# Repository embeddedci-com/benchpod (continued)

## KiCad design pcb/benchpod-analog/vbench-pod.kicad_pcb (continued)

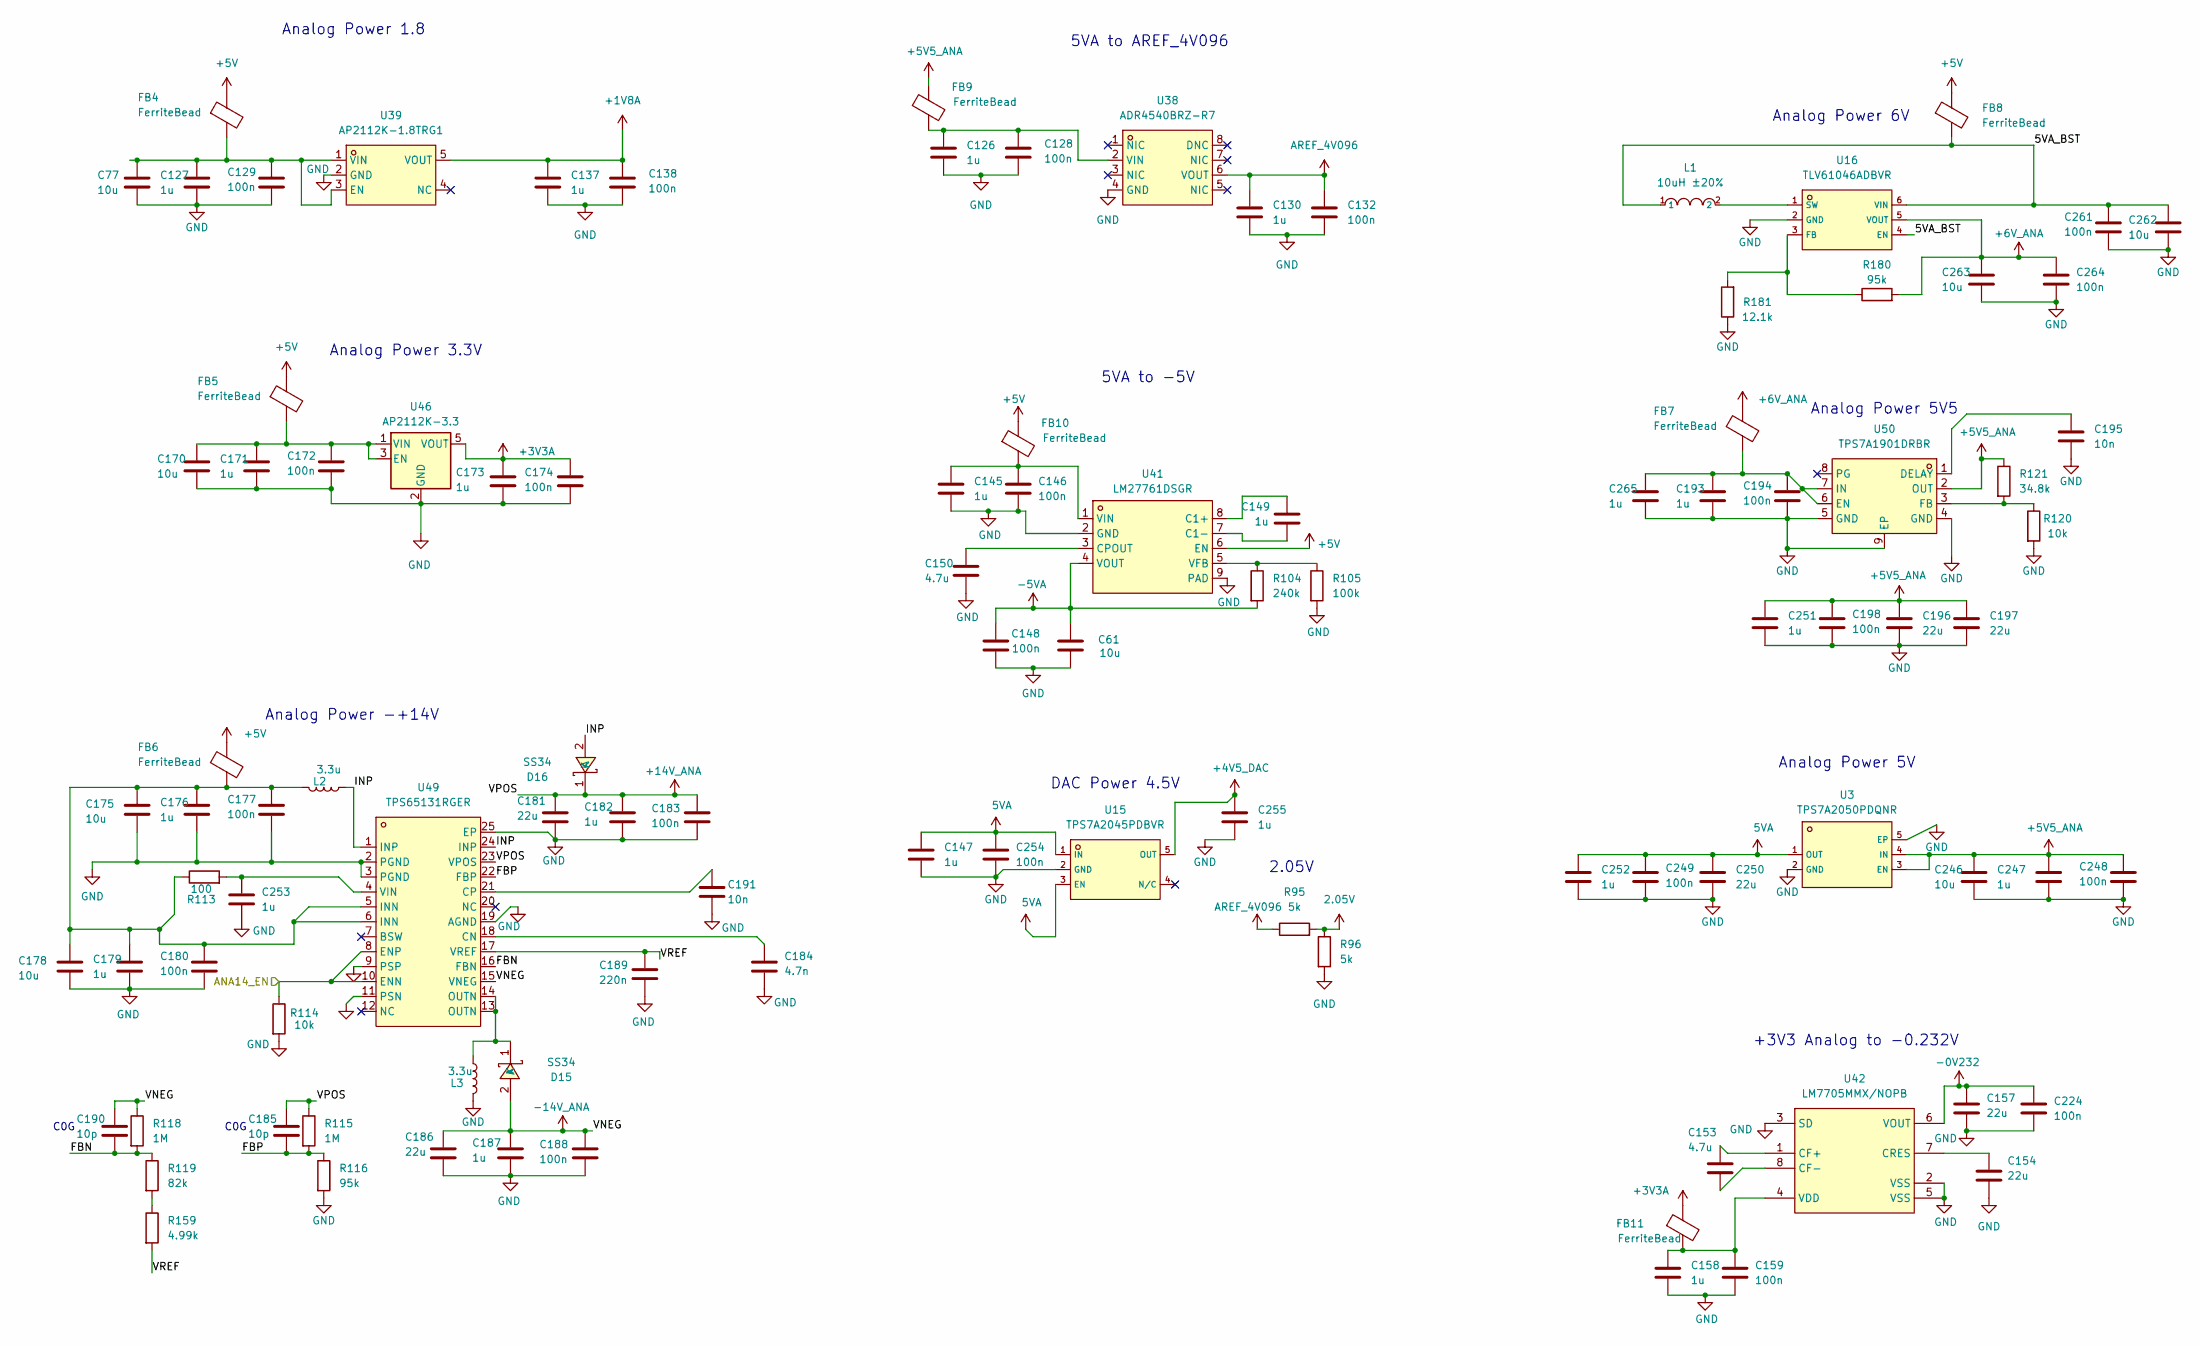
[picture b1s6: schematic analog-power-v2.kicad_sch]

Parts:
C61: 10u; C_0603_1608Metric; LCSC C96446
C77, C170, C175, C178, C246, C262, C263: 10u; C_0603_1608Metric; MPN GRM21BR61H106KE43L; LCSC C96446
C126, C130, C137, C145, C149, C158, C173, C176, C179, C182, C187, C193, C253, C255, C265: 1u; C_0402_1005Metric; MPN GRM155R61H105KE05D; LCSC C1518208
C127, C147, C171, C247, C251, C252: 1u; C_0402_1005Metric; MPN CL05A105KA5NQNC; LCSC C52923
C128, C129, C132, C138, C146, C148, C159, C172, C174, C177, C180, C183, C188, C194, C198, C224, C248, C249, C254, C261, C264: 100n; C_0402_1005Metric; MPN CC0603KRX7R9BB104; LCSC C307331
C150, C153: 4.7u; C_0805_2012Metric; LCSC C98192
C154, C157, C196, C197, C250: 22u; C_0805_2012Metric; LCSC C45783
C181, C186: 22u; C_0805_2012Metric; MPN CL21B105KBFNNNE; LCSC C45783
C184: 4.7n; C_0402_1005Metric; MPN CC0603KRX7R9BB104; LCSC C1538
C185, C190: 10p; C_0402_1005Metric; LCSC C32949
C189: 220n; C_0603_1608Metric; LCSC C64705
C191, C195: 10n; C_0402_1005Metric; LCSC C15195
D15, D16: SS34; SMA_L4.3-W2.6-LS5.2-RD; MPN SS34; LCSC Part C3014011
FB4, FB5, FB6, FB7, FB8, FB9, FB10, FB11: FerriteBead; C85833_L0603; LCSC C85833
L1: 10uH ±20%; C38117_IND-SMD_L4_0-W4_0; LCSC C38117
L2, L3: 3.3u; IND-SMD_L2.0-W1.6_AOTA-B201610S3R3-101-T; LCSC C42411119
R95, R96: 5k; R_0402_1005Metric; LCSC C5948099
R104: 240k; R_0402_1005Metric; LCSC C64043
R105: 100k; R_0402_1005Metric; LCSC C25741
R113: 100; R_0402_1005Metric; LCSC C25076
R114, R120: 10k; R_0402_1005Metric; LCSC C25744
R115, R118: 1M; R_0603_1608Metric; LCSC C22935
R116, R180: 95k; R_0402_1005Metric; LCSC C22375098
R119: 82k; R_0603_1608Metric; LCSC C23254
R121: 34.8k; R_0402_1005Metric; LCSC C2998092
R159: 4.99k; R_0603_1608Metric; LCSC C23046
R181: 12.1k; R_0402_1005Metric; LCSC C25852
U3: TPS7A2050PDQNR; C2866499_X2SON-4_L1_0-W1_0-P0_65-TL-EP; LCSC C2866499
U15: TPS7A2045PDBVR; C2873627_SOT-23-5_L2_9-W1_6-P0_95-LS2_8-BR; LCSC C2873627
U16: TLV61046ADBVR; C464815_SOT-23-6_L2_9-W1_6-P0_95-LS2_8-BL; LCSC C464815
U38: ADR4540BRZ-R7; SOIC-8_L4.9-W3.9-P1.27-LS6.0-BL; MPN ADR4540BRZ-R7; LCSC Part C404003
U39: AP2112K-1.8TRG1; SOT-25_L3.0-W1.6-P0.95-LS2.8-BL; MPN AP2112K-1.8TRG1; LCSC Part C176944
U41: LM27761DSGR; WSON-8_L2.0-W2.0-P0.65-BL-EP; MPN LM27761DSGR; LCSC Part C129351
U42: LM7705MMX/NOPB; MSOP-8_L3.0-W3.0-P0.65-LS5.0-BL; MPN LM7705MMX/NOPB; LCSC Part C2070761
U46: AP2112K-3.3; SOT-25-5_L2.9-W1.6-P0.95-LS2.8-BL; LCSC C51118
U49: TPS65131RGER; VQFN-24_L4.0-W4.0-P0.50-BL-EP2.5; LCSC Part C87663
U50: TPS7A1901DRBR; TDFN-8_L3.0-W3.0-P0.65-BL-EP; MPN TPS7A1901DRBR; LCSC Part C544334

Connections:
2.05V: R95.2, R96.1; also elsewhere on the board
5VA: C147.2, C249.2, C250.1, C252.2, C254.2, U3.1 (OUT), U15.1 (IN), U15.3 (EN); also elsewhere on the board
+1V8A: C137.2, C138.2, U39.5 (VOUT); also elsewhere on the board
+3V3A: C173.2, C174.2, FB11.1, U46.5 (VOUT); also elsewhere on the board
+4V5_DAC: C255.2, U15.5 (OUT); also elsewhere on the board
+5V: FB4.1, FB5.1, FB6.1, FB8.1, FB10.1, U41.6 (EN); also elsewhere on the board
+5V5_ANA: C196.1, C197.1, C198.2, C246.2, C247.2, C248.2, C251.2, FB9.1, R121.1, U3.3 (EN), U3.4 (IN), U50.2 (OUT); also elsewhere on the board
+6V_ANA: C263.2, C264.2, FB7.1, R180.2, U16.5 (VOUT)
+14V_ANA: C181.2, C182.2, C183.2, C185.1, D16.1 (K), R115.1, U49.23 (VPOS); also elsewhere on the board
-5VA: C61.1, C148.2, R104.2, U41.4 (VOUT); also elsewhere on the board
-14V_ANA: C186.2, C187.2, C188.2, C190.1, D15.2 (A), R118.1, U49.15 (VNEG); also elsewhere on the board
/ANA14_EN: R114.1, U49.8 (ENP), U49.10 (ENN); also elsewhere on the board
/Analog Power v2/5VA_BST: C261.2, C262.2, FB8.2, L1.1, U16.4 (EN), U16.6 (VIN)
/Analog Power v2/FBN: C190.2, R118.2, R119.1, U49.16 (FBN)
/Analog Power v2/FBP: C185.2, R115.2, R116.1, U49.22 (FBP)
/Analog Power v2/INP: D16.2 (A), L2.1, U49.1 (INP), U49.24 (INP)
/Analog Power v2/VREF: C189.2, R159.2, U49.17 (VREF)
AREF_4V096: C130.2, C132.2, R95.1, U38.6 (VOUT); also elsewhere on the board
GND: C61.2, C77.1, C126.1, C127.1, C128.1, C129.1, C130.1, C132.1, C137.1, C138.1, C145.1, C146.1, C147.1, C148.1, C150.2, C154.2, C157.2, C158.1, C159.1, C170.1, C171.1, C172.1, C173.1, C174.1, C175.1, C176.1, C177.1, C178.1, C179.1, C180.1, C181.1, C182.1, C183.1, C184.1, C186.1, C187.1, C188.1, C189.1, C191.2, C193.1, C194.1, C195.2, C196.2, C197.2, C198.1, C224.1, C246.1, C247.1, C248.1, C249.1, C250.2, C251.1, C252.1, C253.1, C254.1, C255.1, C261.1, C262.1, C263.1, C264.1, C265.1, L3.2, R96.2, R105.2, R114.2, R116.2, R120.2, R181.1, U3.2 (GND), U3.5 (EP), U15.2 (GND), U16.2 (GND), U38.4 (GND), U39.2 (GND), U41.2 (GND), U41.9 (PAD), U42.2 (VSS), U42.3 (SD), U42.5 (VSS), U46.2 (GND), U49.2 (PGND), U49.3 (PGND), U49.9 (PSP), U49.11 (PSN), U49.19 (AGND), U49.25 (EP), U50.4 (GND), U50.5 (GND), U50.9 (EP); also elsewhere on the board
unnamed: C175.2, C176.2, C177.2, C178.2, C179.2, C180.2, FB6.2, L2.2, R113.1, U49.5 (INN), U49.6 (INN)
unnamed: D15.1 (K), L3.1, U49.13 (OUTN), U49.14 (OUTN)
unnamed: R119.2, R159.1
unnamed: R180.1, R181.2, U16.3 (FB)
unnamed: L1.2, U16.1 (SW)
unnamed: C126.2, C128.2, FB9.2, U38.2 (VIN)
unnamed: C77.2, C127.2, C129.2, FB4.2, U39.1 (VIN), U39.3 (EN)
unnamed: C149.2, U41.8 (C1+)
unnamed: C149.1, U41.7 (C1-)
unnamed: C150.1, U41.3 (CPOUT)
unnamed: R104.1, R105.1, U41.5 (VFB)
unnamed: C145.2, C146.2, FB10.2, U41.1 (VIN)
unnamed: C153.1, U42.1 (CF+)
unnamed: C153.2, U42.8 (CF-)
unnamed: C154.1, U42.7 (CRES)
unnamed: C158.2, C159.2, FB11.2, U42.4 (VDD)
unnamed: C170.2, C171.2, C172.2, FB5.2, U46.1 (VIN), U46.3 (EN)
unnamed: C184.2, U49.18 (CN)
unnamed: C191.1, U49.21 (CP)
unnamed: C253.2, R113.2, U49.4 (VIN)
unnamed: C195.1, U50.1 (DELAY)
unnamed: C193.2, C194.2, C265.2, FB7.2, U50.6 (EN), U50.7 (IN)
unnamed: R120.1, R121.2, U50.3 (FB)
−0V232: C157.1, C224.2, U42.6 (VOUT); also elsewhere on the board

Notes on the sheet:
5VA to AREF_4V096
Analog Power 6V
DAC Power 4.5V
Analog Power 5V
5VA to -5V
Analog Power 5V5
C0G
2.05V
Analog Power 3.3V
Analog Power 1.8
+3V3 Analog to -0.232V
Analog Power -+14V

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
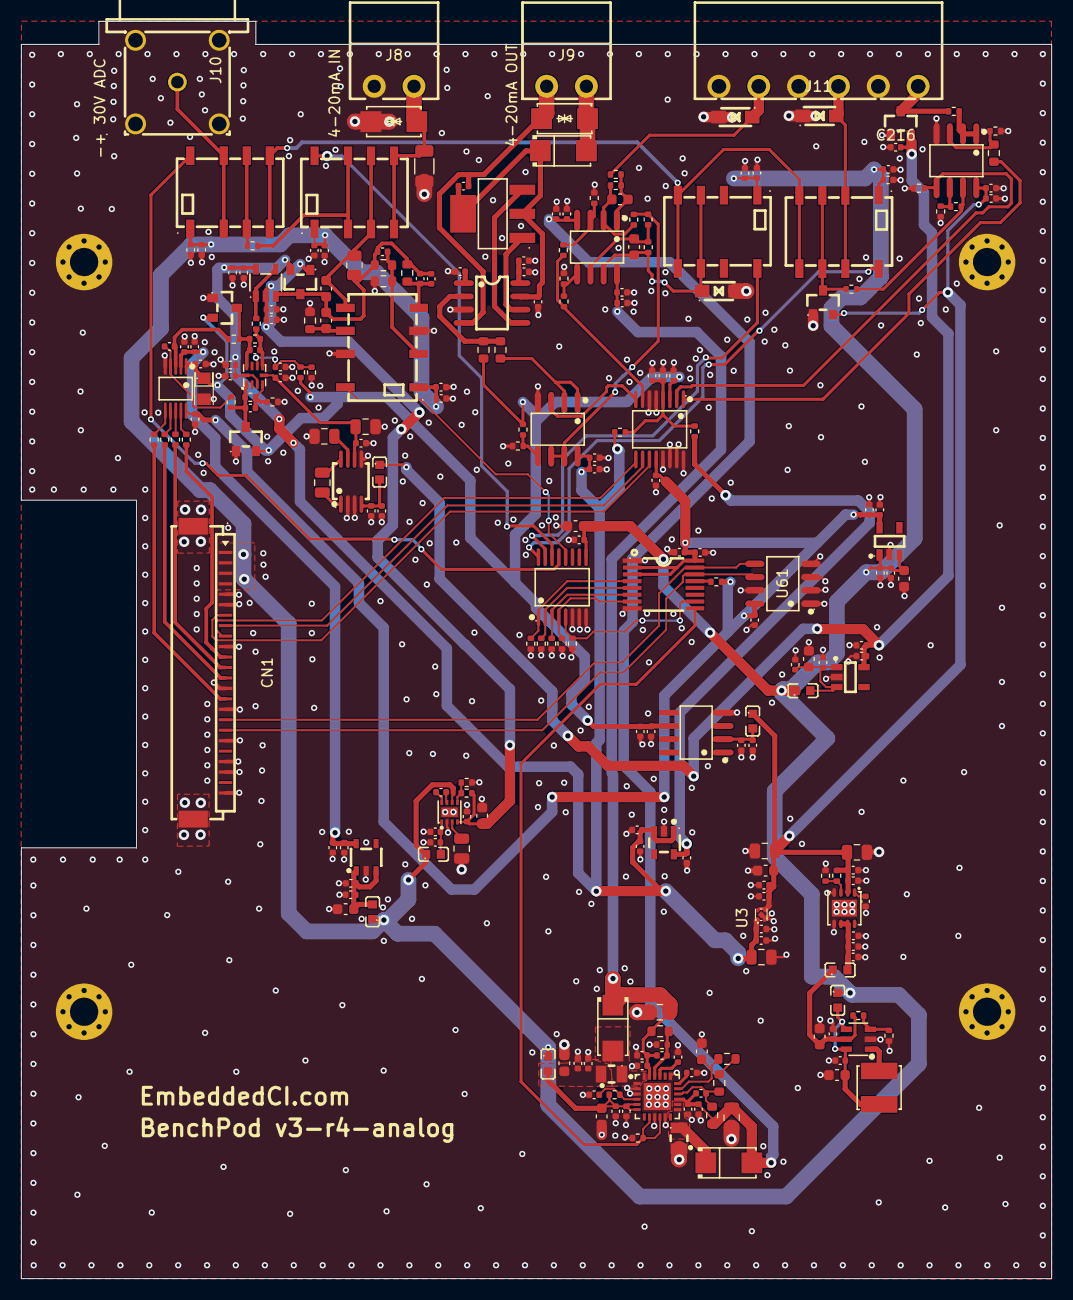
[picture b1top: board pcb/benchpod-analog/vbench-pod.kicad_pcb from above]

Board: 4 copper layers, 98.5 x 120.2 mm, 247 parts (0 on the bottom side), 115 nets.

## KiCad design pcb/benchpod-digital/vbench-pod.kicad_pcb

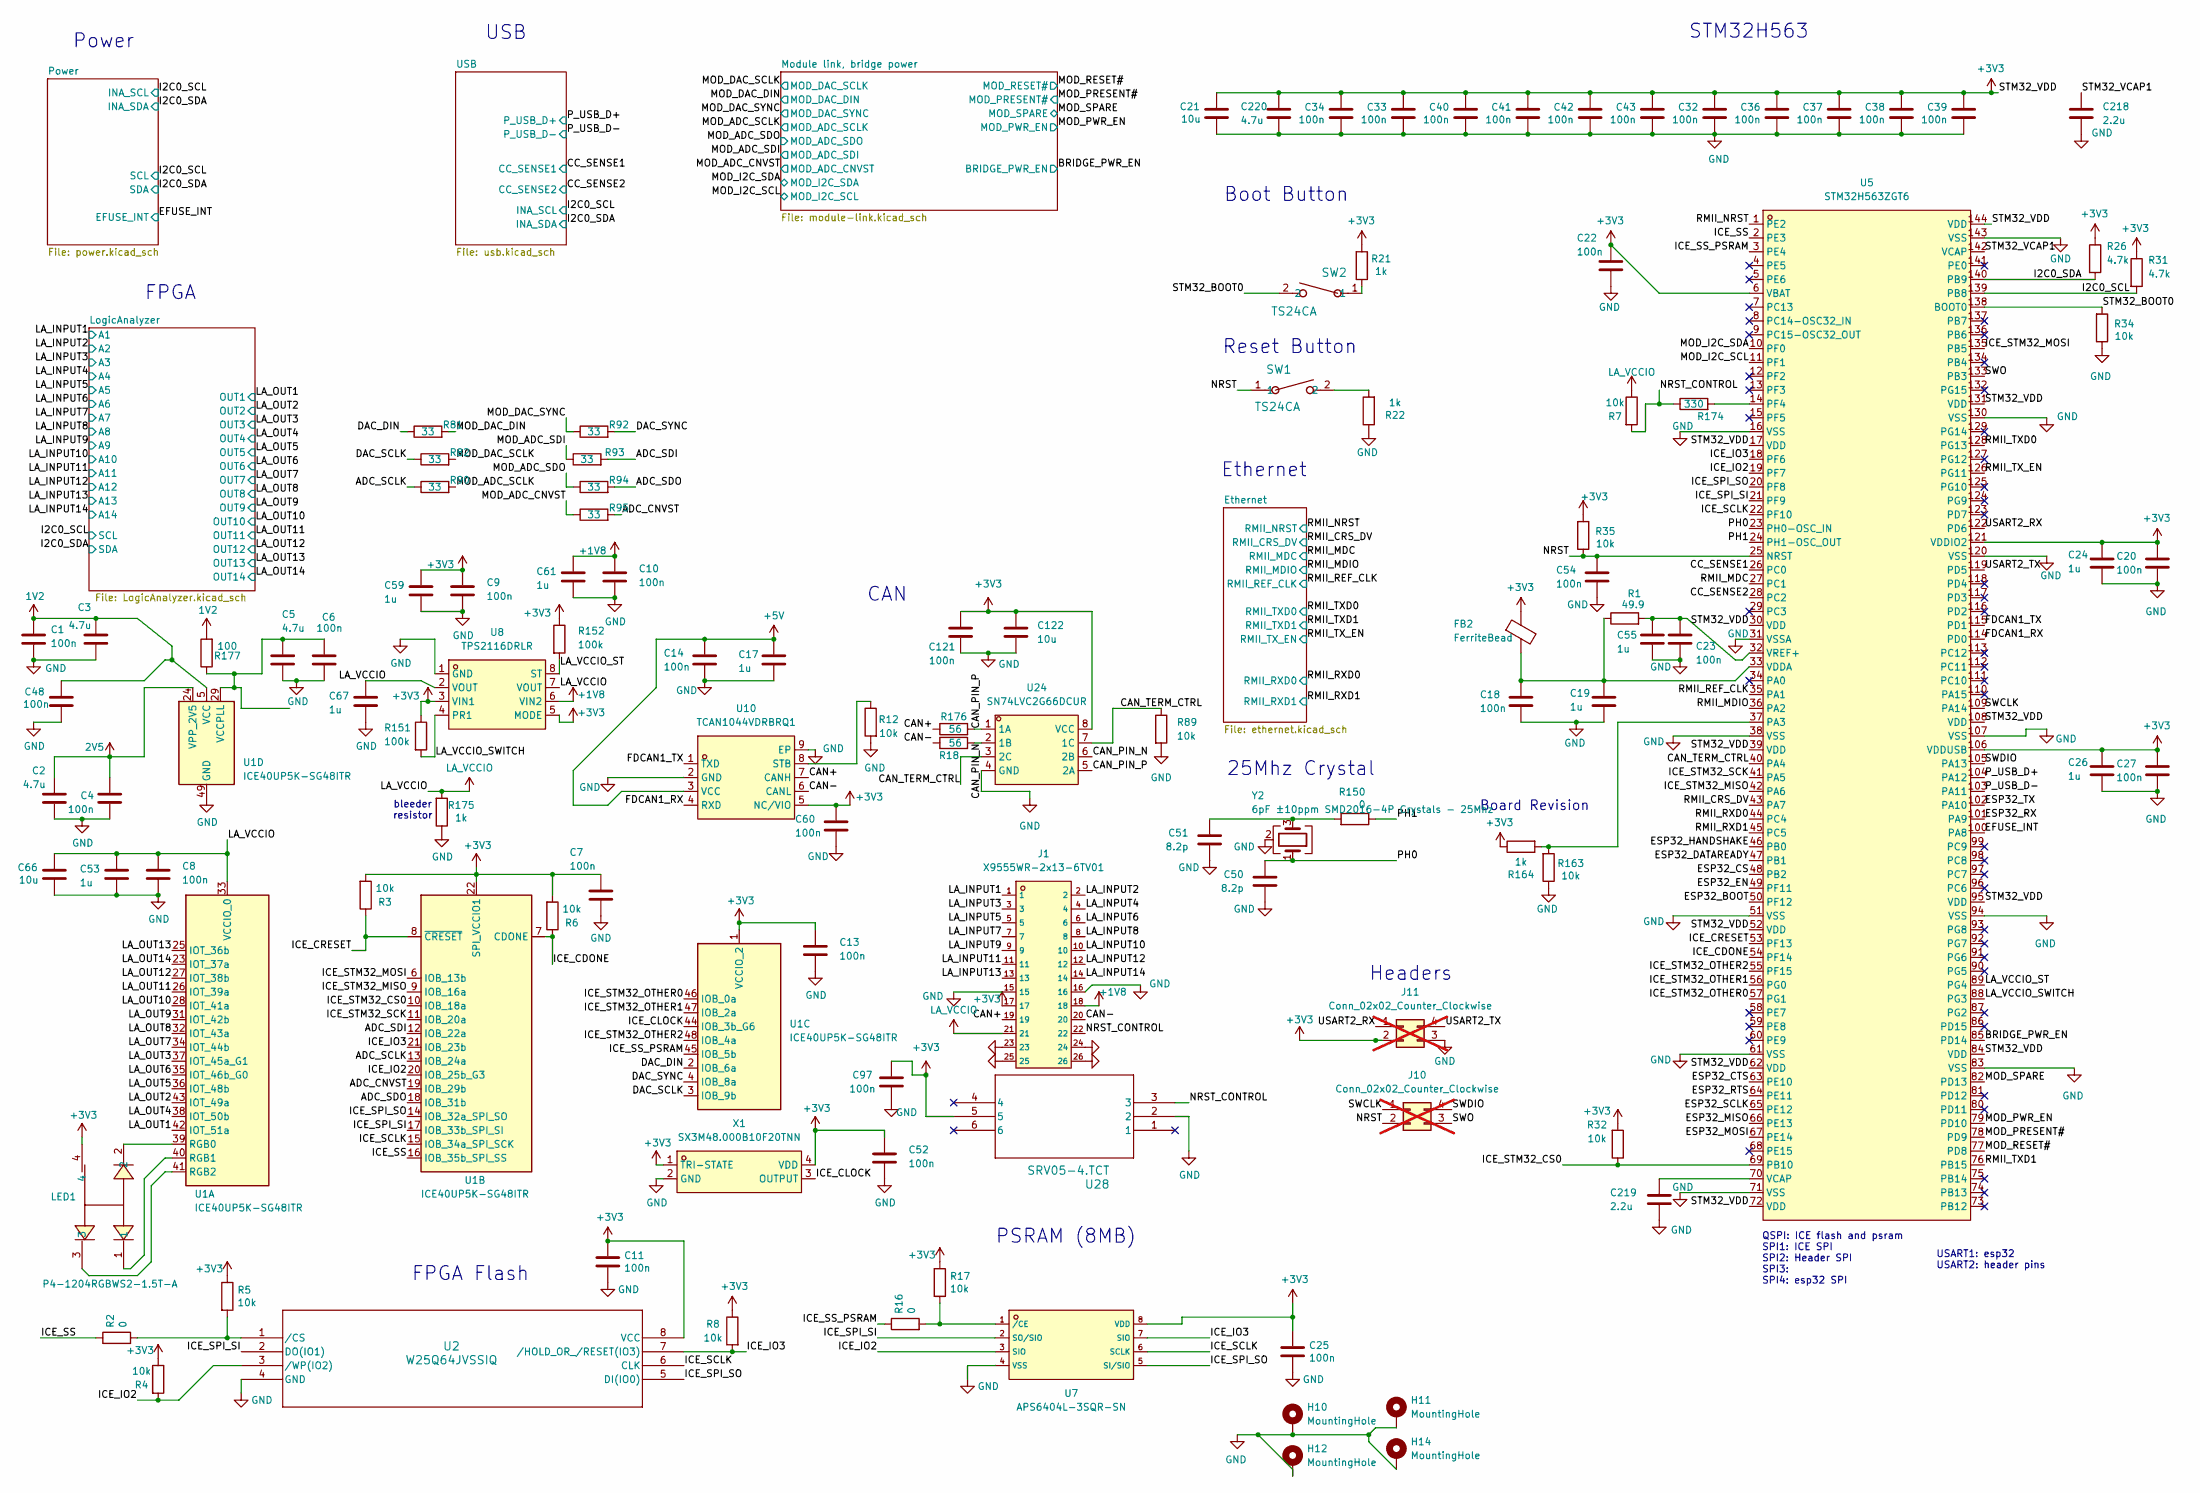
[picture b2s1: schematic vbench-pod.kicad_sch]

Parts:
C1, C4, C6, C7, C8, C9, C10, C13, C14, C18, C20, C22, C23, C27, C48, C52, C54, C60: 100n; C_0402_1005Metric; MPN CC0603KRX7R9BB104; LCSC C307331
C2, C3, C5, C220: 4.7u; C_0805_2012Metric; LCSC C98192
C11, C25, C32, C33, C34, C36, C37, C38, C39, C40, C41, C42, C43, C97, C121: 100n; C_0402_1005Metric; LCSC C307331
C17, C24, C26, C53, C59, C67: 1u; C_0402_1005Metric; MPN CL05A105KA5NQNC; LCSC C52923
C19, C55, C61: 1u; C_0402_1005Metric; MPN GRM155R61H105KE05D; LCSC C1518208
C21, C66, C122: 10u; C_0603_1608Metric; LCSC C96446
C50, C51: 8.2p; C_0402_1005Metric; LCSC C1579
C218, C219: 2.2u; C_0603_1608Metric; LCSC C415535
FB2: FerriteBead; C85833_L0603; LCSC C85833
H10, H11, H12, H14: MountingHole; MountingHole_2.7mm_M2.5_Pad_Via
J1: X9555WR-2x13-6TV01; C2682221_CONN-TH_X9555WR-2X13-6TV01; LCSC C2682221
J10, J11: Conn_02x02_Counter_Clockwise; PinSocket_2x02_P2.54mm_Vertical; not fitted
LED1: P4-1204RGBWS2-1.5T-A; C2827295_LED-SMD_4P-L3.2-W1.5_P4-1204RGBWS2-1.5T-A; MPN P4-1204RGBWS2-1.5T-A; LCSC Part C2827295
R1: 49.9; R_0402_1005Metric; LCSC C325388
R2, R16, R150: 0; R_0402_1005Metric; LCSC C17168
R3, R4, R6, R7, R8, R12, R32, R34, R35, R89, R163: 10k; R_0402_1005Metric; LCSC C25744
R5, R17: 10k; R_0402_1005Metric; JLC_DNF true
R18, R176: 56; R_0402_1005Metric; LCSC C3013179
R21, R22, R164, R175: 1k; R_0402_1005Metric; LCSC C11702
R26, R31: 4.7k; R_0402_1005Metric; LCSC C25900
R81, R82, R90, R92, R93, R94, R95: 33; R_0402_1005Metric; LCSC C25105
R151, R152: 100k; R_0402_1005Metric; LCSC C25741
R174: 330; R_0402_1005Metric; LCSC C25104
R177: 100; R_0402_1005Metric; LCSC C25076
SW1, SW2: TS24CA; C393942_SW-SMD_2P-TS24CA; LCSC C393942
U1: ICE40UP5K-SG48ITR; QFN-48_L7.0-W7.0-P0.50-TL-EP5.4-1; LCSC C2678152
U2: W25Q64JVSSIQ; SOIC-8_L5.3-W5.3-P1.27-LS8.0-BL; MPN W25Q64JVSSIQ; LCSC C179171
U5: STM32H563ZGT6; LQFP-144_L20.0-W20.0-P0.50-LS22.0-TL; LCSC Part C29271104
U7: APS6404L-3SQR-SN; C5333729_SOIC-8_L4.9-W3.9-P1.27-LS6.0-BL; LCSC C5333729
U8: TPS2116DRLR; SOT-583-8_L2.1-W1.6-P0.50-LS1.6-BL; MPN TPS2116DRLR; LCSC Part C3235557
U10: TCAN1044VDRBRQ1; VSON-8_L3.0-W3.0-P0.65-BR-EP; MPN TCAN1044VDRBRQ1; LCSC Part C5215851
U24: SN74LVC2G66DCUR; VSSOP-8_L2.1-W2.4-P0.50-LS3.2-BR; MPN SN74LVC2G66DCUR; LCSC Part C181970
U28: SRV05-4.TCT; SOT-23-6_L2.9-W1.6-P0.95-LS2.8-BR; LCSC C13612
X1: SX3M48.000B10F20TNN; OSC-SMD_4P-L3.2-W2.5-BL; MPN SX3M48.000B10F20TNN; LCSC Part C5452690
Y2: 6pF ±10ppm SMD2016-4P Crystals - 25Mhz; Crystal_SMD_2016-4Pin_2.0x1.6mm; LCSC C49867546

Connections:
1V2: C1.2, C3.1, C48.2, R177.2, U1.5 (VCC), U1.30 (VCC); also elsewhere on the board
2V5: C2.1, C4.2, U1.24 (VPP_2V5); also elsewhere on the board
+1V8: C10.2, C61.2, J1.18, U8.6 (VIN2); also elsewhere on the board
+3V3: C7.2, C9.2, C11.1, C13.2, C20.2, C21.1, C22.2, C24.2, C25.1, C26.2, C27.2, C32.1, C33.1, C34.1, C36.1, C37.1, C38.1, C39.1, C40.1, C41.1, C42.1, C43.1, C52.2, C59.2, C60.2, C97.2, C121.1, C122.2, C220.1, FB2.1, J1.17, J11.2, LED1.4, R3.2, R4.1, R5.1, R6.2, R8.1, R17.1, R21.2, R26.1, R31.1, R32.2, R35.2, R151.1, R152.1, R164.1, U1.1 (VCCIO_2), U1.22 (SPI_VCCIO1), U2.8 (VCC), U5.6 (VBAT), U5.17 (VDD), U5.30 (VDD), U5.39 (VDD), U5.52 (VDD), U5.62 (VDD), U5.72 (VDD), U5.84 (VDD), U5.95 (VDD), U5.106 (VDDUSB), U5.108 (VDD), U5.121 (VDDIO2), U5.131 (VDD), U5.144 (VDD), U7.8 (VDD), U8.3 (VIN1), U8.5 (MODE), U10.5 (NC/VIO), U24.8 (VCC), U28.5, X1.1 (TRI-STATE), X1.4 (VDD); also elsewhere on the board
+5V: C14.2, C17.2, U10.3 (VCC); also elsewhere on the board
/ADC_CNVST: R95.2, U1.19 (IOB_29b)
/ADC_SCLK: R90.1, U1.13 (IOB_24a)
/ADC_SDI: R93.2, U1.12 (IOB_22a)
/ADC_SDO: R94.2, U1.18 (IOB_31b)
/BRIDGE_PWR_EN: U5.85 (PD14); also elsewhere on the board
/CAN+: J1.19, R176.1, U10.7 (CANH)
/CAN-: J1.20, R18.1, U10.6 (CANL)
/CAN_PIN_N: R18.2, U24.2 (1B), U24.6 (2B)
/CAN_PIN_P: R176.2, U24.1 (1A), U24.5 (2A)
/CAN_TERM_CTRL: R89.1, U5.40 (PA4), U24.3 (2C), U24.7 (1C)
/CC_SENSE1: U5.26 (PC0); also elsewhere on the board
/CC_SENSE2: U5.28 (PC2); also elsewhere on the board
/DAC_DIN: R81.1, U1.2 (IOB_6a)
/DAC_SCLK: R82.1, U1.3 (IOB_9b)
/DAC_SYNC: R92.2, U1.4 (IOB_8a)
/EFUSE_INT: U5.100 (PA8); also elsewhere on the board
/ESP32_BOOT: U5.50 (PF12)
/ESP32_CS: U5.48 (PB2)
/ESP32_CTS: U5.63 (PE10)
/ESP32_DATAREADY: U5.47 (PB1)
/ESP32_EN: U5.49 (PF11)
/ESP32_HANDSHAKE: U5.46 (PB0)
/ESP32_MISO: U5.66 (PE13)
/ESP32_MOSI: U5.67 (PE14)
/ESP32_RTS: U5.64 (PE11)
/ESP32_RX: U5.101 (PA9)
/ESP32_SCLK: U5.65 (PE12)
/ESP32_TX: U5.102 (PA10)
/FDCAN1_RX: U5.114 (PD0), U10.4 (RXD)
/FDCAN1_TX: U5.115 (PD1), U10.1 (TXD)
/I2C0_SCL: R31.2, U5.139 (PB8); also elsewhere on the board
/I2C0_SDA: R26.2, U5.140 (PB9); also elsewhere on the board
/ICE_CDONE: R6.1, U1.7 (CDONE), U5.54 (PF14)
/ICE_CLOCK: U1.44 (IOB_3b_G6), X1.3 (OUTPUT)
/ICE_CRESET: R3.1, U1.8 (~CRESET), U5.53 (PF13)
/ICE_IO2: R4.2, U1.20 (IOB_25b_G3), U2.3 (/WP(IO2)), U5.19 (PF7), U7.3 (SIO)
/ICE_IO3: R8.2, U1.21 (IOB_23b), U2.7 (/HOLD_OR_/RESET(IO3)), U5.18 (PF6), U7.7 (SIO)
/ICE_SCLK: U1.15 (IOB_34a_SPI_SCK), U2.6 (CLK), U5.22 (PF10), U7.6 (SCLK)
/ICE_SPI_SI: U1.17 (IOB_33b_SPI_SI), U2.2 (DO(IO1)), U5.21 (PF9), U7.2 (SO/SIO)
/ICE_SPI_SO: U1.14 (IOB_32a_SPI_SO), U2.5 (DI(IO0)), U5.20 (PF8), U7.5 (SI/SIO)
/ICE_SS: R2.1, U1.16 (IOB_35b_SPI_SS), U5.2 (PE3)
/ICE_SS_PSRAM: R16.1, U1.45 (IOB_5b), U5.3 (PE4)
/ICE_STM32_CS0: R32.1, U1.10 (IOB_18a), U5.69 (PB10)
/ICE_STM32_MISO: U1.9 (IOB_16a), U5.42 (PA6)
/ICE_STM32_MOSI: U1.6 (IOB_13b), U5.135 (PB5)
/ICE_STM32_OTHER0: U1.46 (IOB_0a), U5.57 (PG1)
/ICE_STM32_OTHER1: U1.47 (IOB_2a), U5.56 (PG0)
/ICE_STM32_OTHER2: U1.48 (IOB_4a), U5.55 (PF15)
/ICE_STM32_SCK: U1.11 (IOB_20a), U5.41 (PA5)
/LA_INPUT1: J1.1; also elsewhere on the board
/LA_INPUT2: J1.2; also elsewhere on the board
/LA_INPUT3: J1.3; also elsewhere on the board
/LA_INPUT4: J1.4; also elsewhere on the board
/LA_INPUT5: J1.5; also elsewhere on the board
/LA_INPUT6: J1.6; also elsewhere on the board
/LA_INPUT7: J1.7; also elsewhere on the board
/LA_INPUT8: J1.8; also elsewhere on the board
/LA_INPUT9: J1.9; also elsewhere on the board
/LA_INPUT10: J1.10; also elsewhere on the board
/LA_INPUT11: J1.11; also elsewhere on the board
/LA_INPUT12: J1.12; also elsewhere on the board
/LA_INPUT13: J1.13; also elsewhere on the board
/LA_INPUT14: J1.14; also elsewhere on the board
/LA_OUT1: U1.42 (IOT_51a); also elsewhere on the board
/LA_OUT2: U1.43 (IOT_49a); also elsewhere on the board
/LA_OUT3: U1.37 (IOT_45a_G1); also elsewhere on the board
/LA_OUT4: U1.38 (IOT_50b); also elsewhere on the board
/LA_OUT5: U1.36 (IOT_48b); also elsewhere on the board
/LA_OUT6: U1.35 (IOT_46b_G0); also elsewhere on the board
/LA_OUT7: U1.34 (IOT_44b); also elsewhere on the board
/LA_OUT8: U1.32 (IOT_43a); also elsewhere on the board
/LA_OUT9: U1.31 (IOT_42b); also elsewhere on the board
/LA_OUT10: U1.28 (IOT_41a); also elsewhere on the board
/LA_OUT11: U1.26 (IOT_39a); also elsewhere on the board
/LA_OUT12: U1.27 (IOT_38b); also elsewhere on the board
/LA_OUT13: U1.25 (IOT_36b); also elsewhere on the board
/LA_OUT14: U1.23 (IOT_37a); also elsewhere on the board
/LA_VCCIO_ST: R152.2, U5.89 (PG4), U8.8 (ST)
/LA_VCCIO_SWITCH: R151.2, U5.88 (PG3), U8.4 (PR1)
/MOD_ADC_CNVST: R95.1; also elsewhere on the board
/MOD_ADC_SCLK: R90.2; also elsewhere on the board
/MOD_ADC_SDI: R93.1; also elsewhere on the board
/MOD_ADC_SDO: R94.1; also elsewhere on the board
/MOD_DAC_DIN: R81.2; also elsewhere on the board
/MOD_DAC_SCLK: R82.2; also elsewhere on the board
/MOD_DAC_SYNC: R92.1; also elsewhere on the board
/MOD_I2C_SCL: U5.11 (PF1); also elsewhere on the board
/MOD_I2C_SDA: U5.10 (PF0); also elsewhere on the board
/MOD_PRESENT#: U5.78 (PD9); also elsewhere on the board
/MOD_PWR_EN: U5.79 (PD10); also elsewhere on the board
/MOD_RESET#: U5.77 (PD8); also elsewhere on the board
/MOD_SPARE: U5.82 (PD13); also elsewhere on the board
/NRST: C54.2, J10.2, R35.1, SW1.1, U5.25 (NRST)
/NRST_CONTROL: J1.22, R7.2, R174.1, U28.3
/PH0: C50.1, U5.23 (PH0-OSC_IN), Y2.1
/PH1: R150.1, U5.24 (PH1-OSC_OUT)
/P_USB_D+: U5.104 (PA12); also elsewhere on the board
/P_USB_D-: U5.103 (PA11); also elsewhere on the board
/RMII_CRS_DV: U5.43 (PA7); also elsewhere on the board
/RMII_MDC: U5.27 (PC1); also elsewhere on the board
/RMII_MDIO: U5.36 (PA2); also elsewhere on the board
/RMII_NRST: U5.1 (PE2); also elsewhere on the board
/RMII_REF_CLK: U5.35 (PA1); also elsewhere on the board
/RMII_RXD0: U5.44 (PC4); also elsewhere on the board
/RMII_RXD1: U5.45 (PC5); also elsewhere on the board
/RMII_TXD0: U5.128 (PG13); also elsewhere on the board
/RMII_TXD1: U5.76 (PB15); also elsewhere on the board
/RMII_TX_EN: U5.126 (PG11); also elsewhere on the board
/STM32_BOOT0: R34.2, SW2.2, U5.138 (BOOT0)
/STM32_VCAP1: C218.1, U5.142 (VCAP)
/SWCLK: J10.1, U5.109 (PA14)
/SWDIO: J10.4, U5.105 (PA13)
/SWO: J10.3, U5.133 (PB3)
/USART2_RX: J11.1, U5.122 (PD6)
/USART2_TX: J11.4, U5.119 (PD5)
GND: C1.1, C2.2, C3.2, C4.1, C5.1, C6.1, C7.1, C8.1, C9.1, C10.1, C11.2, C13.1, C14.1, C17.1, C18.1, C19.1, C20.1, C21.2, C22.1, C23.1, C24.1, C25.2, C26.1, C27.1, C32.2, C33.2, C34.2, C36.2, C37.2, C38.2, C39.2, C40.2, C41.2, C42.2, C43.2, C48.1, C50.2, C51.2, C52.1, C53.1, C54.1, C55.1, C59.1, C60.1, C61.1, C66.2, C67.1, C97.1, C121.2, C122.1, C218.2, C219.2, C220.2, H10.1 (1_1), H11.1 (1_1), H12.1 (1_1), H14.1 (1_1), J1.15, J1.16, J1.23, J1.24, J1.25, J1.26, J11.3, R12.2, R22.1, R34.1, R89.2, R163.1, R175.1, U1.49 (GND), U2.4 (GND), U5.16 (VSS), U5.31 (VSSA), U5.38 (VSS), U5.51 (VSS), U5.61 (VSS), U5.71 (VSS), U5.83 (VSS), U5.94 (VSS), U5.107 (VSS), U5.120 (VSS), U5.130 (VSS), U5.143 (VSS), U7.4 (VSS), U8.1 (GND), U10.2 (GND), U10.9 (EP), U24.4 (GND), U28.2, X1.2 (GND), Y2.2 (G), Y2.4 (G); also elsewhere on the board
LA_VCCIO: C8.2, C53.2, C66.1, C67.2, J1.21, R7.1, R175.2, U1.33 (VCCIO_0), U8.2 (VOUT), U8.7 (VOUT); also elsewhere on the board
unnamed: C51.1, R150.2, Y2.3
unnamed: C219.1, U5.70 (VCAP)
unnamed: R21.1, SW2.1
unnamed: R22.2, SW1.2
unnamed: LED1.2, U1.39 (RGB0)
unnamed: LED1.1, U1.40 (RGB1)
unnamed: LED1.3, U1.41 (RGB2)
unnamed: C5.2, C6.2, R177.1, U1.29 (VCCPLL)
unnamed: R2.2, R5.2, U2.1 (/CS)
unnamed: R163.2, R164.2, U5.37 (PA3)
unnamed: R174.2, U5.14 (PF4)
unnamed: C18.2, C19.2, FB2.2, R1.1, U5.33 (VDDA)
unnamed: C23.2, C55.2, R1.2, U5.32 (VREF+)
unnamed: R16.2, R17.2, U7.1 (/CE)
unnamed: R12.1, U10.8 (STB)

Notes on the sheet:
bleeder resistor
CAN
QSPI: ICE flash and psram SPI1: ICE SPI SPI2: Header SPI SPI3: SPI4: esp32 SPI
STM32H563
USB
Ethernet
25Mhz Crystal
Reset Button
FPGA Flash
FPGA
Boot Button
Headers
USART1: esp32 USART2: header pins
PSRAM (8MB)
Power
Board Revision

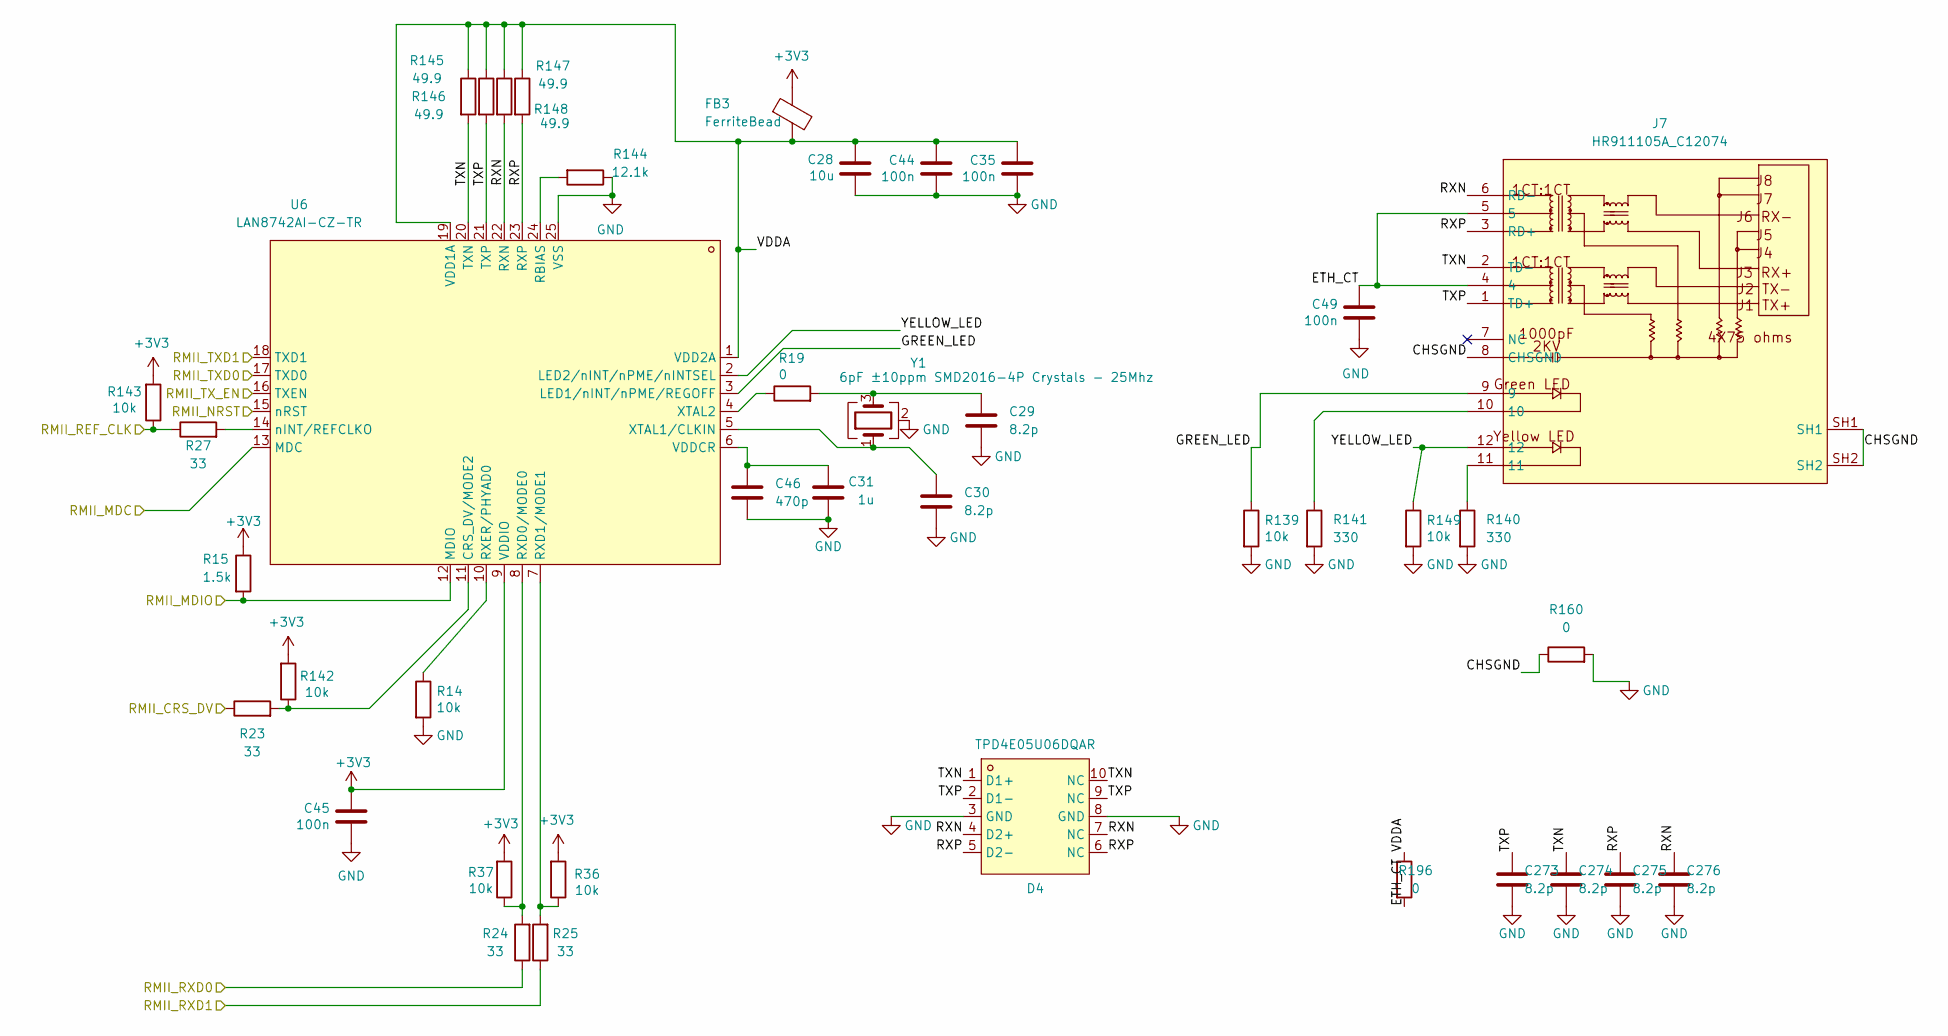
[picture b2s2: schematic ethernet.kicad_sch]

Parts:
C28: 10u; C_0603_1608Metric; LCSC C96446
C29, C30, C273, C274, C275, C276: 8.2p; C_0402_1005Metric; LCSC C1579
C31: 1u; C_0402_1005Metric; MPN GRM155R61H105KE05D; LCSC C1518208
C35, C44, C45, C49: 100n; C_0402_1005Metric; LCSC C307331
C46: 470p; C_0402_1005Metric; LCSC C1537
D4: TPD4E05U06DQAR; C138714_USON-10_L2.5-W1.0-P0.50-BL; LCSC C138714
FB3: FerriteBead; C85833_L0603; LCSC C85833
J7: HR911105A_C12074; RJ45-TH_HR911105A; MPN HR911105A; LCSC Part C12074
R14, R139, R149: 10k; R_0402_1005Metric; JLC_DNF true
R15: 1.5k; R_0402_1005Metric; LCSC C25867
R19, R160, R196: 0; R_0402_1005Metric; LCSC C17168
R23, R24, R25, R27: 33; R_0402_1005Metric; LCSC C25105
R36, R37, R142, R143: 10k; R_0402_1005Metric; LCSC C25744
R140, R141: 330; R_0402_1005Metric; LCSC C25104
R144: 12.1k; R_0402_1005Metric; LCSC C25852
R145, R146, R147, R148: 49.9; R_0402_1005Metric; LCSC C325388
U6: LAN8742AI-CZ-TR; VQFN-24_L4.0-W4.0-P0.50-BL-EP2.5; MPN LAN8742AI-CZ-TR; LCSC Part C621425
Y1: 6pF ±10ppm SMD2016-4P Crystals - 25Mhz; Crystal_SMD_2016-4Pin_2.0x1.6mm; LCSC C49867546

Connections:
+3V3: C45.1, FB3.1, R15.1, R36.2, R37.2, R142.2, R143.2, U6.9 (VDDIO); also elsewhere on the board
/Ethernet/CHSGND: J7.8 (CHSGND), J7.SH1, J7.SH2, R160.1
/Ethernet/ETH_CT: C49.1, J7.4, J7.5, R196.2
/Ethernet/GREEN_LED: J7.9, R139.1, U6.3 (LED1/nINT/nPME/REGOFF)
/Ethernet/RXN: C276.1, D4.4 (D2+), D4.7 (NC), J7.6 (RD-), R147.2, U6.22 (RXN)
/Ethernet/RXP: C275.1, D4.5 (D2-), D4.6 (NC), J7.3 (RD+), R148.2, U6.23 (RXP)
/Ethernet/TXN: C274.1, D4.1 (D1+), D4.10 (NC), J7.2 (TD-), R145.2, U6.20 (TXN)
/Ethernet/TXP: C273.1, D4.2 (D1-), D4.9 (NC), J7.1 (TD+), R146.2, U6.21 (TXP)
/Ethernet/VDDA: C28.1, C35.1, C44.1, FB3.2, R145.1, R146.1, R147.1, R148.1, R196.1, U6.1 (VDD2A), U6.19 (VDD1A)
/Ethernet/YELLOW_LED: J7.12, R149.1, U6.2 (LED2/nINT/nPME/nINTSEL)
/RMII_CRS_DV: R23.1; also elsewhere on the board
/RMII_MDC: U6.13 (MDC); also elsewhere on the board
/RMII_MDIO: R15.2, U6.12 (MDIO); also elsewhere on the board
/RMII_NRST: U6.15 (nRST); also elsewhere on the board
/RMII_REF_CLK: R27.1, R143.1; also elsewhere on the board
/RMII_RXD0: R24.1; also elsewhere on the board
/RMII_RXD1: R25.1; also elsewhere on the board
/RMII_TXD0: U6.17 (TXD0); also elsewhere on the board
/RMII_TXD1: U6.18 (TXD1); also elsewhere on the board
/RMII_TX_EN: U6.16 (TXEN); also elsewhere on the board
GND: C28.2, C29.2, C30.2, C31.1, C35.2, C44.2, C45.2, C46.2, C49.2, C273.2, C274.2, C275.2, C276.2, D4.3 (GND), D4.8 (GND), R14.2, R139.2, R140.2, R141.2, R144.1, R149.2, R160.2, U6.25 (VSS), Y1.2 (G), Y1.4 (G); also elsewhere on the board
unnamed: C29.1, R19.2, Y1.3
unnamed: J7.10, R141.1
unnamed: J7.11, R140.1
unnamed: R23.2, R142.1, U6.11 (CRS_DV/MODE2)
unnamed: R144.2, U6.24 (RBIAS)
unnamed: R24.2, R37.1, U6.8 (RXD0/MODE0)
unnamed: R25.2, R36.1, U6.7 (RXD1/MODE1)
unnamed: R14.1, U6.10 (RXER/PHYAD0)
unnamed: C31.2, C46.1, U6.6 (VDDCR)
unnamed: C30.1, U6.5 (XTAL1/CLKIN), Y1.1
unnamed: R19.1, U6.4 (XTAL2)
unnamed: R27.2, U6.14 (nINT/REFCLKO)
